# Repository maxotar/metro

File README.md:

# Metro - Vibrating Metronome Wearable

A compact wearable metronome device that provides haptic feedback for keeping time. Perfect for musicians, dancers, and other performers who need portable tempo guidance.

## Project Metadata

- **Project Name:** Metro
- **Type:** Wearable Device
- **Primary Function:** Vibrating Metronome
- **Target MCU:** ATtiny1616
- **CPU Frequency:** 4 MHz
- **Battery:** 302025 LiPo
- **Charging:** Smart ring magnetic pogo pin connector

## Project Structure

### `/electrical`
PCB design files, schematics, and component information
- KiCad project files (.kicad_sch, .kicad_pcb)
- Component library with footprints and datasheets
- Fabrication and production files (BOM, designators, netlist)

### `/src`
Firmware for the ATtiny1616 microcontroller
- `main.cpp` - Main program entry point
- `i2c.cpp` - I2C communication library

### `/mechanical`
Enclosure and mechanical design
- `Case.step` - 3D model of the device case
- [Onshape CAD](https://cad.onshape.com/documents/80829a8af30c2a989428d6ff/w/00026b4066893ecc4d2da063/e/4930d11ba89da00962c1ae8d?renderMode=0&uiState=69bccf33683487e6bda76e25) - Full source CAD file

**3D Printing Specifications:**
- Printer: Bambu Lab A1
- Material: Matte white PLA
- Bed: Smooth PEI surface
- Nozzle: 0.2 mm
- Layer height: 0.06 mm (high quality)
- Print method: Parts printed individually (case, back cap, buttons) for quality assurance

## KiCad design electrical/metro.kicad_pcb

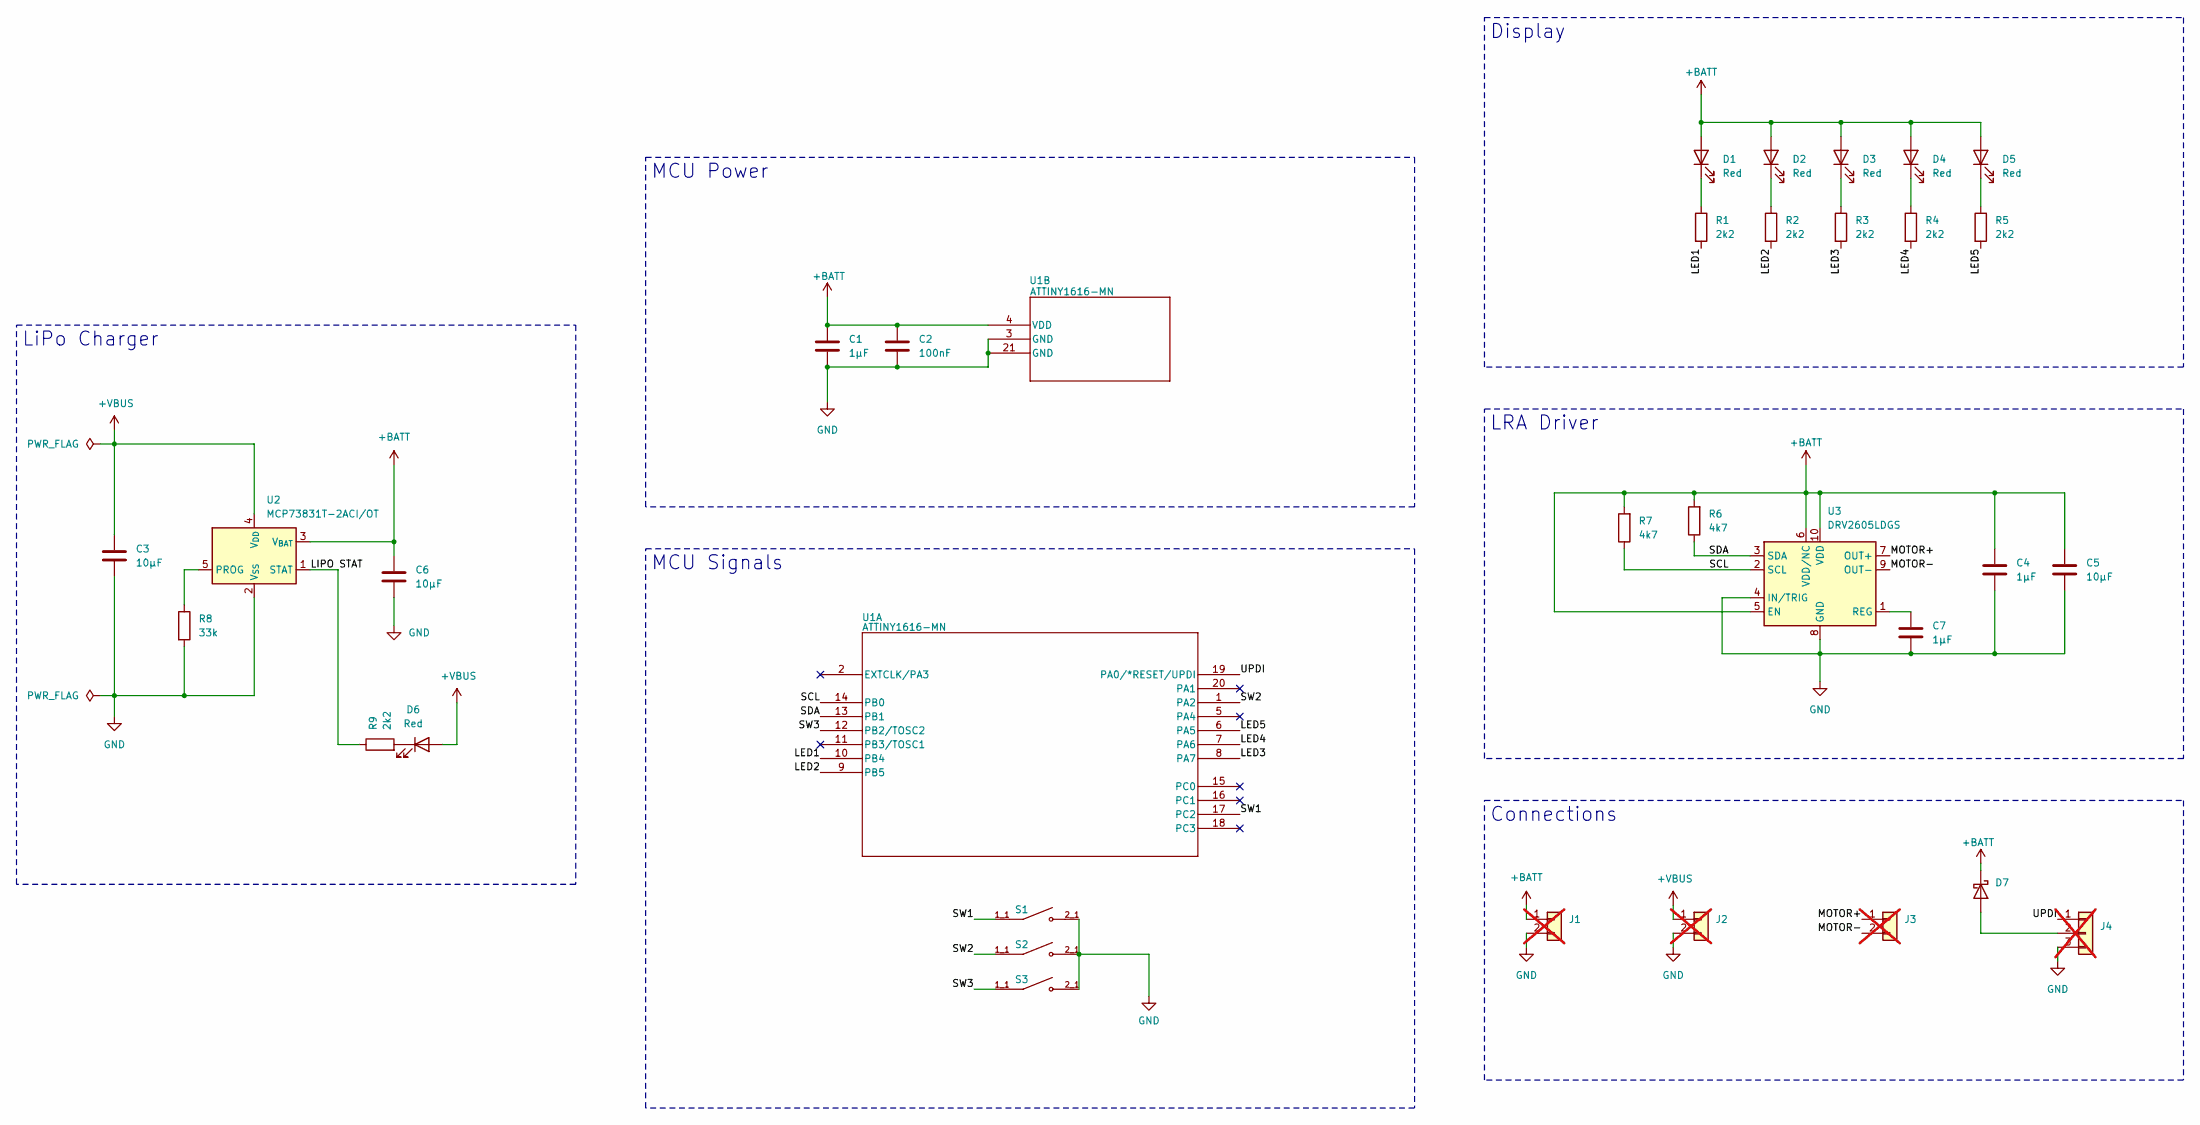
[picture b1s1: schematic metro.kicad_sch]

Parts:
C1, C4, C7: 1μF; C_0603_1608Metric_Pad1.08x0.95mm_HandSolder
C2: 100nF; C_0603_1608Metric_Pad1.08x0.95mm_HandSolder
C3, C5, C6: 10μF; C_0603_1608Metric_Pad1.08x0.95mm_HandSolder
D1, D2, D3, D4, D5, D6: Red; Custom LTST-C230KRKT; LCSC PN C125107
D7: D_Schottky; D_SMA
J1, J2, J3: Conn_01x02; PinHeader_1x02_P2.54mm_Vertical; not fitted
J4: Conn_01x03; PinHeader_1x03_P2.54mm_Vertical; not fitted
R1, R2, R3, R4, R5, R9: 2k2; R_0603_1608Metric_Pad0.98x0.95mm_HandSolder
R6, R7: 4k7; R_0603_1608Metric_Pad0.98x0.95mm_HandSolder
R8: 33k; R_0603_1608Metric_Pad0.98x0.95mm_HandSolder
S1, S2, S3: EVQ-P7C01P; SW_EVQ-P7C01P; LCSC PN C388883
U1: ATTINY1616-MN; VQFN20_REB_MCH; LCSC PN C507118
U2: MCP73831T-2ACI/OT; SOT-23-5; LCSC PN C424093
U3: DRV2605LDGS; VSSOP-10_3x3mm_P0.5mm; LCSC PN C527464

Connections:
+BATT: C1.1, C2.1, C4.1, C5.1, C6.1, D1.2 (A), D2.2 (A), D3.2 (A), D4.2 (A), D5.2 (A), D7.1 (K), J1.1, R6.2, R7.2, U1.4 (VDD), U2.3 (V_{BAT}), U3.5 (EN), U3.6 (VDD/NC), U3.10 (VDD)
+VBUS: C3.1, D6.2 (A), J2.1, U2.4 (V_{DD})
/LED1: R1.2, U1.10 (PB4)
/LED2: R2.2, U1.9 (PB5)
/LED3: R3.2, U1.8 (PA7)
/LED4: R4.2, U1.7 (PA6)
/LED5: R5.2, U1.6 (PA5)
/LIPO STAT: R9.1, U2.1 (STAT)
/MOTOR+: J3.1, U3.7 (OUT+)
/MOTOR-: J3.2, U3.9 (OUT-)
/SCL: R7.1, U1.14 (PB0), U3.2 (SCL)
/SDA: R6.1, U1.13 (PB1), U3.3 (SDA)
/SW1: S1.1_1, S1.1_2, U1.17 (PC2)
/SW2: S2.1_1, S2.1_2, U1.1 (PA2)
/SW3: S3.1_1, S3.1_2, U1.12 (PB2/TOSC2)
/UPDI: J4.1, U1.19 (PA0/*RESET/UPDI)
GND: C1.2, C2.2, C3.2, C4.2, C5.2, C6.2, C7.2, J1.2, J2.2, J4.3, R8.2, S1.2_1, S1.2_2, S2.2_1, S2.2_2, S3.2_1, S3.2_2, U1.3 (GND), U1.21 (GND), U2.2 (V_{SS}), U3.4 (IN/TRIG), U3.8 (GND)
unnamed: D1.1 (K), R1.1
unnamed: D2.1 (K), R2.1
unnamed: D3.1 (K), R3.1
unnamed: D4.1 (K), R4.1
unnamed: D5.1 (K), R5.1
unnamed: D6.1 (K), R9.2
unnamed: D7.2 (A), J4.2
unnamed: R8.1, U2.5 (PROG)
unnamed: C7.1, U3.1 (REG)

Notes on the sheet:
MCU Signals
Display
LiPo Charger
LRA Driver
MCU Power
Connections

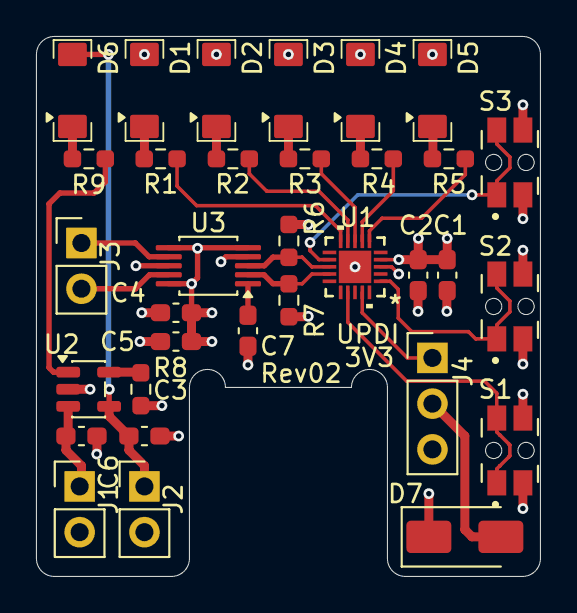
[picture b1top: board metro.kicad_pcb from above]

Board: 4 copper layers, 28.0 x 30.0 mm, 33 parts (0 on the bottom side), 26 nets.

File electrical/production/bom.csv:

Designator,Footprint,Quantity,Value,LCSC Part #
"C1, C4, C7",0603,3,1μF,
C2,0603,1,100nF,
"C3, C5, C6",0603,3,10μF,
"D1, D2, D3, D4, D5, D6",Custom LTST-C230KRKT,6,Red,C125107
D7,D_SMA,1,D_Schottky,
"R1, R2, R3, R4, R5, R9",0603,6,2k2,
"R6, R7",0603,2,4k7,
R8,0603,1,33k,
"S1, S2, S3",SW_EVQ-P7C01P,3,EVQ-P7C01P,C388883
U1,VQFN20_REB_MCH,1,ATTINY1616-MN,C507118
U2,SOT-23-5,1,MCP73831T-2ACI/OT,C424093
U3,VSSOP-10_3x3mm_P0.5mm,1,DRV2605LDGS,C527464

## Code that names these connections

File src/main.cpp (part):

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   -------+-------------+----------------+-----------+-------------------------
   VDD  4 | Power       | Power supply   | -         | Connect to 3.3V/5V
   GND  3 | Ground      | Ground         | -         | Common ground
   PA0 19 | UPDI        | Programming    | -         | Reserved for UPDI
   PA1 20 | -           | FREE           | -         | Available
   PA2  1 | SW2         | Play/Pause     | Input     | Internal pullup, FALLING
   PA3  2 | -           | FREE           | -         | Available
   PA4  5 | -           | FREE           | -         | Available
   PB4 10 | LED1 (LSB)  | LED bit 0      | Output    | Active low
   PB5  9 | LED2        | LED bit 1      | Output    | Active low
   PA7  8 | LED3        | LED bit 2      | Output    | Active low
   PB0 14 | TWI0 SCL    | I2C Clock      | I2C       | 4.7kΩ pullup
   PB1 13 | TWI0 SDA    | I2C Data       | I2C       | 4.7kΩ pullup
   PB2 12 | SW3         | Increase BPM   | Input     | Internal pullup, FALLING
   PB3 11 | -           | FREE           | -         | Available
   PA5  6 | LED5 (MSB)  | LED bit 4      | Output    | Active low
   PA6  7 | LED4        | LED bit 3      | Output    | Active low
   PC0 15 | -           | FREE           | -         | Available
   PC1 16 | -           | FREE           | -         | Available
   PC2 17 | SW1         | Decrease BPM   | Input     | Internal pullup, FALLING
   PC3 18 | -           | FREE           | -         | Available

   Used: 11 pins (3 buttons + 5 BPM LEDs + 2 I2C + 1 UPDI)
   Free:  7 pins (PA1, PA3, PA4, PB3, PC0, PC1, PC3)
   Power: 2 pins (VDD, GND)
   Total: 20
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};

static Button buttons[] = {
    {PIN2_bm, &PORTC, &PORTC.PIN2CTRL, TASK_BTN_DEC_DEBOUNCE, action_dec},         // SW1 - PC2 - Decrease BPM
    {PIN2_bm, &PORTA, &PORTA.PIN2CTRL, TASK_BTN_PLAY_DEBOUNCE, action_play_pause}, // SW2 - PA2 - Play/Pause
    {PIN2_bm, &PORTB, &PORTB.PIN2CTRL, TASK_BTN_INC_DEBOUNCE, action_inc},         // SW3 - PB2 - Increase BPM
};

/* software-extended 32‑bit RTC tick counter; incremented on every
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#define TASK_PENDING (1 << 0)

// BPM Display LEDs (5 bits, scaled by 5) - all active low
// LED5 is MSB (bit 4) on PA5, LED4 bit 3 on PA6, LED3 bit 2 on PA7.
// LED2 bit 1 on PB5, LED1 is LSB bit 0 on PB4.
// Weighted values: PA5=80, PA6=40, PA7=20, PB5=10, PB4=5.
#define LED5_PIN PIN5_bm // PA5 - bit 4 (MSB)
#define LED4_PIN PIN6_bm // PA6 - bit 3
#define LED3_PIN PIN7_bm // PA7 - bit 2
#define LED2_PIN PIN5_bm // PB5 - bit 1
#define LED1_PIN PIN4_bm // PB4 - bit 0 (LSB)

// Timing constants (in RTC ticks at 32kHz, 1 tick = 0.030517578125 ms)
#define DEBOUNCE_DELAY 1966   // ~60 ms
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
static void init_unused_pins_low_power(void)
{
  // PA1, PA3, PA4 are free (PA2=SW2, PA5-PA7=BPM LEDs)
  PORTA.OUTCLR = PIN1_bm | PIN3_bm | PIN4_bm;
  PORTA.DIRSET = PIN1_bm | PIN3_bm | PIN4_bm;
  PORTA.PIN1CTRL = PORT_ISC_INPUT_DISABLE_gc;
  PORTA.PIN3CTRL = PORT_ISC_INPUT_DISABLE_gc;
  PORTA.PIN4CTRL = PORT_ISC_INPUT_DISABLE_gc;

  // PB3 is free (PB2 is now SW3)
  PORTB.OUTCLR = PIN3_bm;
  PORTB.DIRSET = PIN3_bm;
  PORTB.PIN3CTRL = PORT_ISC_INPUT_DISABLE_gc;

  // PC0, PC1, PC3 are free (PC2 is now SW1)
  PORTC.OUTCLR = PIN0_bm | PIN1_bm | PIN3_bm;
  PORTC.DIRSET = PIN0_bm | PIN1_bm | PIN3_bm;
  PORTC.PIN0CTRL = PORT_ISC_INPUT_DISABLE_gc;
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
static void init_leds(void)
{
  // Configure LED pins as outputs on PORTA (MSB bits: PA5, PA6, PA7)
  PORTA.DIRSET = LED5_PIN | LED4_PIN | LED3_PIN;
  PORTA.OUTSET = LED5_PIN | LED4_PIN | LED3_PIN; // Start HIGH (LEDs off - active low)

  // Configure LED pins as outputs on PORTB (LSB bits: PB4, PB5)
  PORTB.DIRSET = LED1_PIN | LED2_PIN;
  PORTB.OUTSET = LED1_PIN | LED2_PIN; // Start HIGH (LEDs off - active low)
}

static void show_bpm(void)
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  // Scale BPM to a 5-bit display value: 0..31 represents BPM_MIN..BPM_MAX in steps of 5
  uint8_t scaled = bpm / 5;

  led_set(&PORTB, LED1_PIN, (scaled & 0x01) != 0);
  led_set(&PORTB, LED2_PIN, (scaled & 0x02) != 0);
  led_set(&PORTA, LED3_PIN, (scaled & 0x04) != 0);
  led_set(&PORTA, LED4_PIN, (scaled & 0x08) != 0);
  led_set(&PORTA, LED5_PIN, (scaled & 0x10) != 0);
}

static void schedule_task(uint8_t task, uint16_t delay)
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{
  (void)ctx;
  // blank all BPM LEDs (active low)
  PORTB.OUTSET = LED1_PIN | LED2_PIN;
  PORTA.OUTSET = LED3_PIN | LED4_PIN | LED5_PIN;
}

static void task_haptic_standby(void *ctx)
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
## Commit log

2026-01-04 add bulk of electrical project
2026-01-15 Basic vibration with breakout board
2026-01-18 functional but without sleep
2026-01-18 working with standby but on button2
2026-01-18 working with i2c stuff in it
2026-01-19 working again, some debug funcs added
2026-01-19 power down working, still only play button
2026-01-19 buttons work, slightly glitchy
2026-01-19 Improve i2c functions, and button interrupts. add ERM i2c function
2026-01-19 minor refactoring
2026-01-19 add watchdog when awake
2026-01-19 possibly safer init_rtc
2026-01-20 massive refactor to scheduler
2026-01-21 even bigger refactor. working LRA, blocking hapric
2026-01-24 Circuit mostly complete with driver
2026-01-26 new led setup
2026-01-29 Routing done
2026-01-29 shift things away from edges, remove dead tracks
2026-01-30 Improve led footprint
2026-01-31 pcb purchased
2026-02-24 working on breadboard
2026-02-24 remove status led
2026-02-25 rev 2 board. larger components
2026-02-28 increase rtc lcok speed. order board rev 2
2026-03-01 fix timing math and pinout bugs
2026-03-20 fix led order, improve debounce
2026-03-20 project completed!
